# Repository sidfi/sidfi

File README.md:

# SIDfi

SIDfi is a single-board self-contained SID file player. SIDfi requires the original MOS 6581 chip or a pin-compatible replacement such as [ARMSID](https://www.nobomi.cz/8bit/armsid/index_en.php). SIDfi plays tune files such as [High Voltage SID Collection](https://hvsc.c64.org/) from a FAT-formatted memory card and displays current tune information on a small LCD screen. Buttons on the LCD screen can be used to control the playback.

## Design Notes

- Emulates MOS 6502 on PIC32MX270F256 microcontroller using [MOS6502 library](https://github.com/gianlucag/mos6502);
- Firmware built with Microchip MPLAB v5.45 and XC32 v2.50;
- [Waveshare 1.44inch LCD HAT](https://www.waveshare.com/1.44inch-lcd-hat.htm) and [ST7735S library](https://github.com/bersch/ST7735S) for display and control;
- [Waveshare Micro SD Storage Board](https://www.waveshare.com/micro-sd-storage-board.htm) and [FatFs library](http://www.elm-chan.org/fsw/ff/00index_e.html) for memory card support;
- 2N3904 transistor for audio amplifier;
- Standard 3mm headset jack for audio output;
- USB 2.0 Type-B connector for 5V power supply (consumes 300mA).

## Schematics

## PCB rendering

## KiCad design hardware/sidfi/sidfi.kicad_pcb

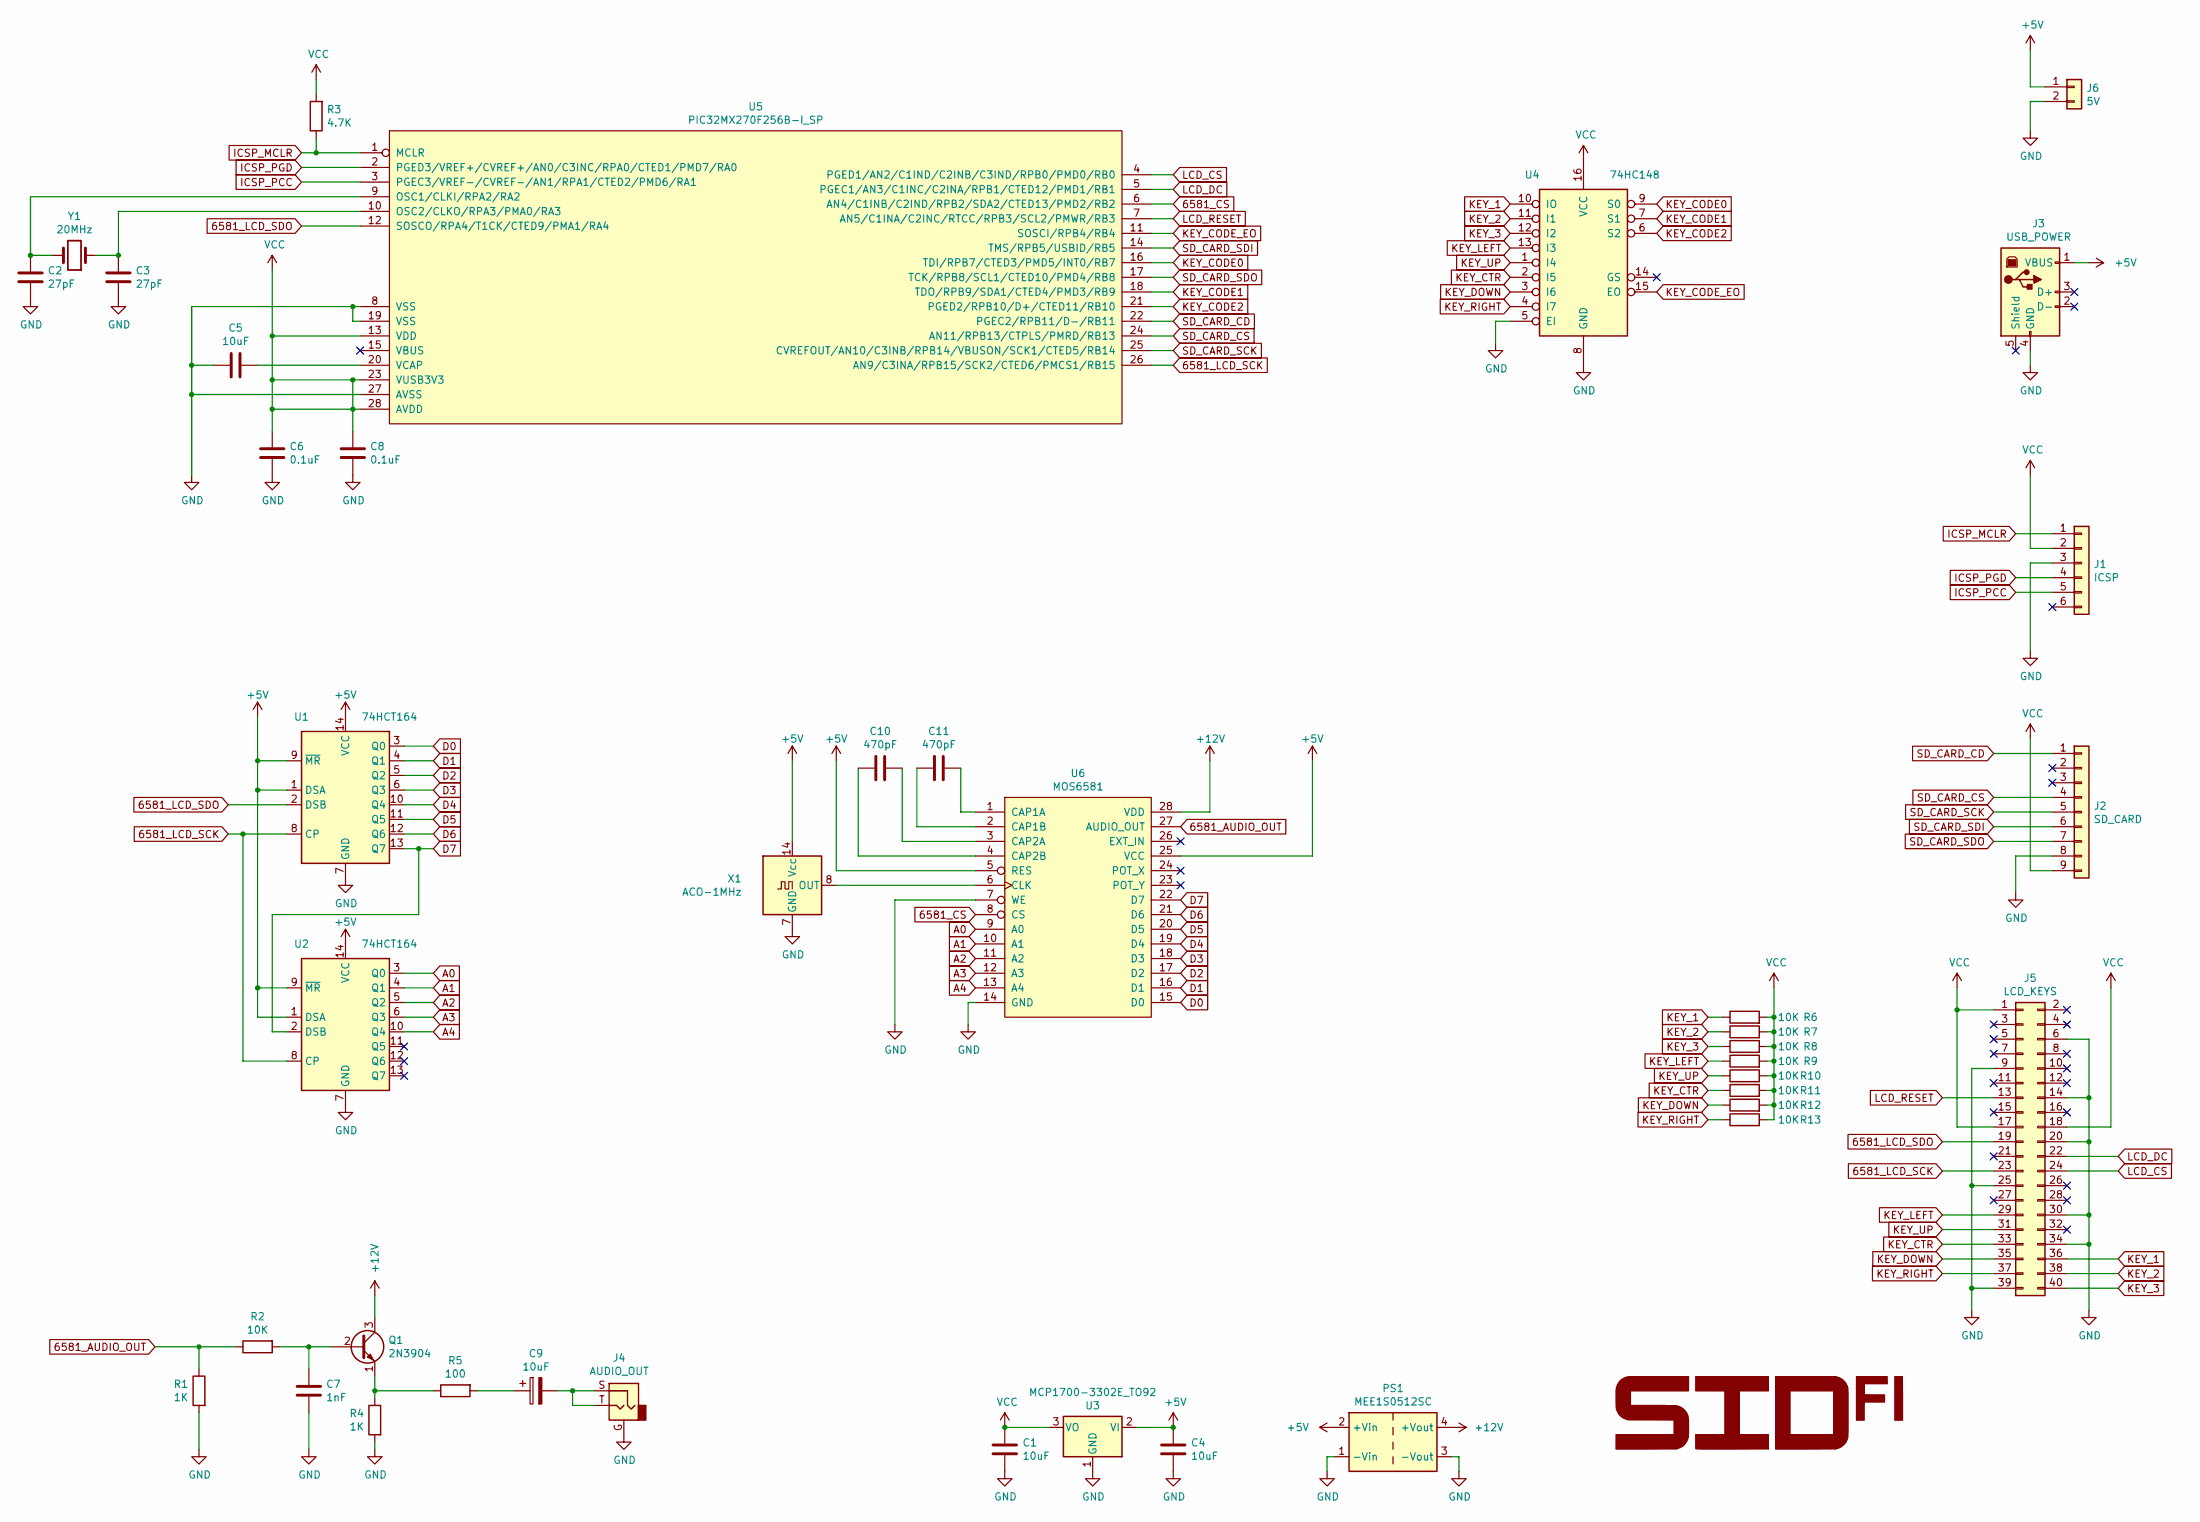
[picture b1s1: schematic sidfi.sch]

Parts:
C1, C4, C5: 10uF; C_Disc_D5.0mm_W2.5mm_P5.00mm
C2, C3: 27pF; C_Disc_D5.0mm_W2.5mm_P5.00mm
C6, C8: 0.1uF; C_Disc_D5.0mm_W2.5mm_P5.00mm
C7: 1nF; C_Disc_D5.0mm_W2.5mm_P5.00mm
C9: 10uF; CP_Radial_D4.0mm_P1.50mm
C10, C11: 470pF; C_Disc_D5.0mm_W2.5mm_P5.00mm
J1: ICSP; PinHeader_1x06_P2.54mm_Vertical
J2: SD_CARD; PinSocket_1x09_P2.54mm_Horizontal
J3: USB_POWER; CUI_UJ2-BH-1-TH
J4: AUDIO_OUT; CUI_SJ1-3523NG
J5: LCD_KEYS; PinHeader_2x20_P2.54mm_Vertical
J6: 5V; PinHeader_1x02_P2.54mm_Vertical
PS1: MEE1S0512SC; Converter_DCDC_Murata_MEE1SxxxxSC_THT
Q1: 2N3904; TO-92_HandSolder
R1, R4: 1K; R_Axial_DIN0207_L6.3mm_D2.5mm_P7.62mm_Horizontal
R2, R6, R7, R8, R9, R10, R11, R12, R13: 10K; R_Axial_DIN0207_L6.3mm_D2.5mm_P7.62mm_Horizontal
R3: 4.7K; R_Axial_DIN0207_L6.3mm_D2.5mm_P7.62mm_Horizontal
R5: 100; R_Axial_DIN0207_L6.3mm_D2.5mm_P7.62mm_Horizontal
U1, U2: 74HCT164; DIP-14_W7.62mm
U3: MCP1700-3302E_TO92; TO-92_HandSolder
U4: 74HC148; DIP-16_W7.62mm
U5: PIC32MX270F256B-I_SP; DIP-28_W7.62mm_Socket
U6: MOS6581; DIP-28_W15.24mm
X1: ACO-1MHz; Oscillator_DIP-14
Y1: 20MHz; Crystal_HC49-U_Vertical

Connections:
6581_AUDIO_OUT: R1.1, R2.1, U6.27 (AUDIO_OUT)
6581_CS: U5.6 (AN4/C1INB/C2IND/RPB2/SDA2/CTED13/PMD2/R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), U6.8 (CS)
6581_LCD_SCK: J5.23, U1.8 (CP), U2.8 (CP), U5.26 (AN9/C3INA/RPB15/SCK2/CTED6/PMCS1/RB15)
6581_LCD_SDO: J5.19, U1.2 (DSB), U5.12 (SOSCO/RPA4/T1CK/CTED9/PMA1/RA4)
+5V: C4.1, J3.1 (VBUS), J6.1, PS1.2 (+Vin), U1.1 (DSA), U1.9 (~MR), U1.14 (VCC), U2.1 (DSA), U2.9 (~MR), U2.14 (VCC), U3.2 (VI), U6.5 (RES), U6.25 (VCC), X1.14 (Vcc)
+12V: PS1.4 (+Vout), Q1.3 (C), U6.28 (VDD)
A0: U2.3 (Q0), U6.9 (A0)
A1: U2.4 (Q1), U6.10 (A1)
A2: U2.5 (Q2), U6.11 (A2)
A3: U2.6 (Q3), U6.12 (A3)
A4: U2.10 (Q4), U6.13 (A4)
D0: U1.3 (Q0), U6.15 (D0)
D1: U1.4 (Q1), U6.16 (D1)
D2: U1.5 (Q2), U6.17 (D2)
D3: U1.6 (Q3), U6.18 (D3)
D4: U1.10 (Q4), U6.19 (D4)
D5: U1.11 (Q5), U6.20 (D5)
D6: U1.12 (Q6), U6.21 (D6)
D7: U1.13 (Q7), U2.2 (DSB), U6.22 (D7)
GND: C1.2, C2.2, C3.2, C4.2, C5.2, C6.2, C7.2, C8.2, J1.3, J2.8, J3.4 (GND), J4.G, J5.6, J5.9, J5.14, J5.20, J5.25, J5.30, J5.34, J5.39, J6.2, PS1.1 (-Vin), PS1.3 (-Vout), R1.2, R4.2, U1.7 (GND), U2.7 (GND), U3.1 (GND), U4.5 (EI), U4.8 (GND), U5.8 (VSS), U5.19 (VSS), U5.27 (AVSS), U6.7 (WE), U6.14 (GND), X1.7 (GND)
ICSP_MCLR: J1.1, R3.1, U5.1 (MCLR)
ICSP_PCC: J1.5, U5.3 (PGEC3/VREF-/CVREF-/AN1/RPA1/CTED2/PMD6/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)
ICSP_PGD: J1.4, U5.2 (PGED3/VREF+/CVREF+/AN0/C3INC/RPA0/CTED1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)
KEY_1: J5.36, R6.1, U4.10 (IO)
KEY_2: J5.38, R7.1, U4.11 (I1)
KEY_3: J5.40, R8.1, U4.12 (I2)
KEY_CODE0: U4.9 (S0), U5.16 (TDI/RPB7/CTED3/PMD5/INT0/RB7)
KEY_CODE1: U4.7 (S1), U5.18 (TDO/RPB9/SDA1/CTED4/PMD3/RB9)
KEY_CODE2: U4.6 (S2), U5.21 (PGED2/RPB10/D+/CTED11/RB10)
KEY_CODE_EO: U4.15 (EO), U5.11 (SOSCI/RPB4/RB4)
KEY_CTR: J5.33, R11.1, U4.2 (I5)
KEY_DOWN: J5.35, R12.1, U4.3 (I6)
KEY_LEFT: J5.29, R9.1, U4.13 (I3)
KEY_RIGHT: J5.37, R13.1, U4.4 (I7)
KEY_UP: J5.31, R10.1, U4.1 (I4)
LCD_CS: J5.24, U5.4 (PGED1/AN2/C1IND/C2INB/C3IND/RPB0/PMD0/R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)
LCD_DC: J5.22, U5.5 (PGEC1/AN3/C1INC/C2INA/RPB1/CTED12/PMD1/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)
LCD_RESET: J5.13, U5.7 (AN5/C1INA/C2INC/RTCC/RPB3/SCL2/PMWR/RB3)
unnamed: C2.1, U5.9 (OSC1/CLKI/RPA2/RA2), Y1.2
unnamed: C3.1, U5.10 (OSC2/CLKO/RPA3/PMA0/RA3), Y1.1
unnamed: C5.1, U5.20 (VCAP)
unnamed: C7.1, Q1.2 (B), R2.2
unnamed: C9.1, R5.2
unnamed: C9.2, J4.S, J4.T
unnamed: C10.1, U6.3 (CAP2A)
unnamed: C10.2, U6.4 (CAP2B)
unnamed: C11.1, U6.2 (CAP1B)
unnamed: C11.2, U6.1 (CAP1A)
unnamed: Q1.1 (E), R4.1, R5.1
unnamed: U6.6 (CLK), X1.8 (OUT)
SD_CARD_CD: J2.1, U5.22 (PGEC2/RPB11/D-/RB11)
SD_CARD_CS: J2.4, U5.24 (AN11/RPB13/CTPLS/PMRD/RB13)
SD_CARD_SCK: J2.5, U5.25 (CVREFOUT/AN10/C3INB/RPB14/VBUSON/SCK1/C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)
SD_CARD_SDI: J2.6, U5.14 (TMS/RPB5/USBID/RB5)
SD_CARD_SDO: J2.7, U5.17 (TCK/RPB8/SCL1/CTED10/PMD4/RB8)
VCC: C1.1, C6.1, C8.1, J1.2, J2.9, J5.1, J5.17, J5.18, R3.2, R6.2, R7.2, R8.2, R9.2, R10.2, R11.2, R12.2, R13.2, U3.3 (VO), U4.16 (VCC), U5.13 (VDD), U5.23 (VUSB3V3), U5.28 (AVDD)

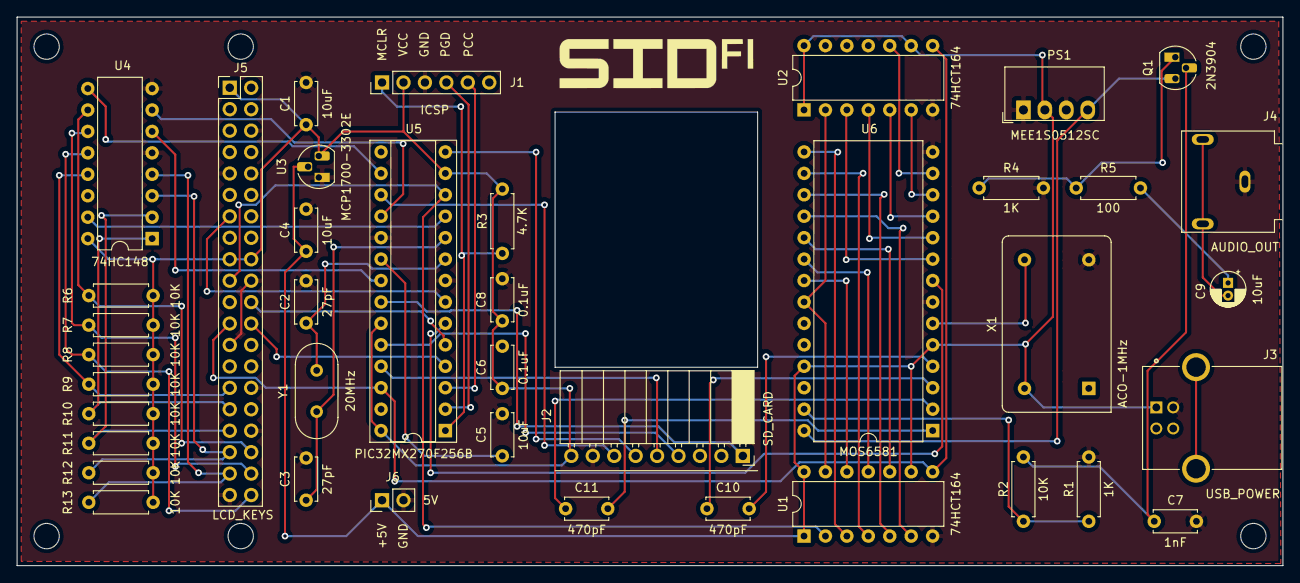
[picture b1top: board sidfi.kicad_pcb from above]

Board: 2 copper layers, 150.0 x 65.0 mm, 40 parts (0 on the bottom side), 56 nets.

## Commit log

2021-04-06 Firmware--WIP
2021-04-11 Play tunes!
2021-04-13 ST7735S display
2021-04-16 Song lengths
2021-04-17 Play multiple songs from one sid file
2021-04-17 Dev env
2021-04-17 Hardware
2021-04-17 Keep song lengths file open
2021-04-19 PCB--WIP
2021-04-19 CUI footprints
2021-04-20 Fix crash when OOM on writing
2021-04-20 Program script
2021-04-20 Route the PCB
2021-04-20 3D render the PCB
2021-04-20 Fix link
2021-04-20 Remove accidental objects in PCB
2021-04-21 Fix traversing files
2021-04-21 Adjust audio connector footprint
2021-04-22 Logo. Redo PCB.
2021-05-15 PCB fixes
2021-05-15 Adjust for Waveshare SD storage board
2021-05-16 Label pins on J1 and J6
2021-05-23 Adjust licenses and README
2021-05-23 Update PCB rendeing

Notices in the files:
hardware/sidfi/sidfi.kicad_pcb:
SIDfi Version 0.1 (c) 2021 Peter Hizalev
